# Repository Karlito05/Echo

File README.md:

# Echo
The best-sounding ortholinear keyboard.

## General Information
This project utilizes three main programs: [Ergogen](https://github.com/ergogen/ergogen), [Autodesk Fusion 360](https://www.autodesk.com/products/fusion-360/overview), and [KiCad](https://www.kicad.org/).

- The `config.yaml` file contains the Ergogen script used to generate the output files.
- 3D model files, including the case, switch plate, and keycaps, are located in the `./3D models` directory. Custom keycaps were modeled due to non-standard sizes.
- The entire keyboard is approximately 7 mm thick (excluding keycaps and switches).

### Why custom keycaps?
The keycaps sizes are not standard. For example in normal sets there is no R3 and R4 3U keycap. So I had to make my own.
## A Quick Overview of Ergogen
Ergogen is a generator utility for ergonomic keyboard layouts, including plates, cases, and PCBs. [Learn more about Ergogen here](https://docs.ergogen.xyz/)

In Ergogen, six main elements are used:
- **Meta**: Metadata
- **Units**: Defines unit-specific configurations
- **Zones**: Configurations for rows and columns
- **Outlines**: Outlines of the keyboard
- **PCBs**: Printed circuit board generation
- **Cases**: Case designs

Each of these elements is subdivided into more specific categories.

## How to Build from the Ergogen File
Follow these steps to build from the Ergogen file:

1. Ensure Ergogen and the `footprints` folder are in the same directory as `config.yaml`.
2. Open your terminal.
3. Navigate to the current working directory using `cd`.
4. Run the command:  
   ```bash
   ergogen .
   ```
This will generate an `output` folder containing the output files.

## Final Build
The keyboard has not been built yet. The plan includes:
- Switches: Lubed Akko Rosewood switches (hot-swap configuration)
- Lubed stabilizers
- Additional Sound-improving modifications

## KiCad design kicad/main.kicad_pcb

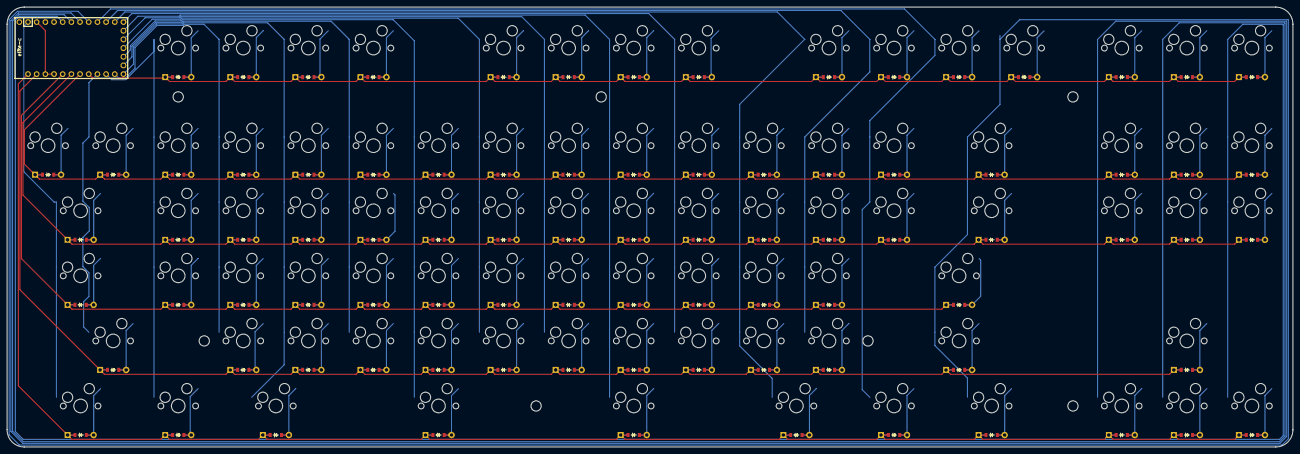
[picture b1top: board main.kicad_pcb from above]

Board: 2 copper layers, 376.4 x 128.8 mm, 174 parts (0 on the bottom side), 111 nets.

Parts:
D1, D2, D3, D4, D5, D6, D7, D8, D9, D10, D11, D12, D13, D14, D15, D16, D17, D18, D19, D20, D21, D22, D23, D24, D25, D26, D27, D28, D29, D30, D31, D32, D33, D34, D35, D36, D37, D38, D39, D40, D41, D42, D43, D44, D45, D46, D47, D48, D49, D50, D51, D52, D53, D54, D55, D56, D57, D58, D59, D60, D61, D62, D63, D64, D65, D66, D67, D68, D69, D70, D71, D72, D73, D74, D75, D76, D77, D78, D79, D80, D81, D82, D83, D84, D85, D86, D87: ComboDiode
S1, S2, S3, S4, S5, S6, S7, S8, S9, S10, S11, S12, S13, S14, S15, S16, S17, S18, S19, S20, S21, S22, S23, S24, S25, S26, S27, S28, S29, S30, S31, S32, S33, S34, S35, S36, S37, S38, S39, S40, S41, S42, S43, S44, S45, S46, S47, S48, S49, S50, S51, S52, S53, S54, S55, S56, S57, S58, S59, S60, S61, S62, S63, S64, S65, S66, S67, S68, S69, S70, S71, S72, S73, S74, S75, S76, S77, S78, S79, S80, S81, S82, S83, S84, S85, S86, S87: MX

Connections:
B0: S47.1, S48.1, S49.1, S55.1
B1: S44.1, S45.1, S61.1, S73.1
B2: S36.1, S37.1, S38.1, S39.1, S60.1, S71.1
B3: S40.1, S41.1, S42.1, S43.1, S72.1
B4: S4.1, S5.1, S6.1, S7.1, S64.1
B5: S8.1, S9.1, S10.1, S11.1, S57.1, S65.1
B6: S32.1, S33.1, S34.1, S35.1, S70.1
B7: S12.1, S13.1, S14.1, S15.1, S66.1
C6: D63.1, D64.1, D65.1, D66.1, D67.1, D68.1, D69.1, D70.1, D71.1, D72.1, D73.1, D74.1, D75.1, D76.1, D77.1
C7: S20.1, S21.1, S22.1, S23.1, S67.1
D0: D2.1, D6.1, D10.1, D14.1, D18.1, D22.1, D26.1, D30.1, D34.1, D38.1, D42.1, D44.1, D48.1, D53.1, D79.1, D83.1, D86.1
D1: D1.1, D5.1, D9.1, D13.1, D17.1, D21.1, D25.1, D29.1, D33.1, D37.1, D41.1, D47.1, D52.1
D2: D4.1, D8.1, D12.1, D16.1, D20.1, D24.1, D28.1, D32.1, D36.1, D40.1, D46.1, D51.1, D82.1
D3: D55.1, D56.1, D57.1, D58.1, D59.1, D60.1, D61.1, D62.1, D78.1, D81.1, D85.1
D4: D3.1, D7.1, D11.1, D15.1, D19.1, D23.1, D27.1, D31.1, D35.1, D39.1, D43.1, D45.1, D49.1, D50.1, D54.1, D80.1, D84.1, D87.1
D5: S16.1, S17.1, S18.1, S19.1, S58.1
D7: S46.1, S50.1
E6: S1.1, S2.1, S3.1, S56.1, S63.1
F0: S28.1, S29.1, S30.1, S31.1, S59.1, S69.1
F1: S24.1, S25.1, S26.1, S27.1, S68.1
F4: S77.1, S85.1, S86.1, S87.1
F5: S76.1, S81.1, S82.1, S83.1, S84.1
F6: S75.1, S78.1, S79.1, S80.1
F7: S51.1, S52.1, S53.1, S54.1, S62.1, S74.1
eight_eight: D31.2, S31.2
eight_i: D30.2, S30.2
eight_k: D29.2, S29.2
eight_m: D28.2, S28.2
eighth_f7: D69.2, S69.2
eleventh_dash: D43.2, S43.2
eleventh_f10: D72.2, S72.2
eleventh_openCurlyBrace: D42.2, S42.2
eleventh_questionMark: D40.2, S40.2
eleventh_quotes: D41.2, S41.2
fifteenth_scrLk: D76.2, S76.2
fifth_f4: D66.2, S66.2
fifth_five: D19.2, S19.2
fifth_g: D17.2, S17.2
fifth_spaceR: D59.2, S59.2
fifth_t: D18.2, S18.2
fifth_v: D16.2, S16.2
first_a: D1.2, S1.2
first_backspace: D54.2, S54.2
first_capsLock: D47.2, S47.2
first_ctrlL: D55.2, S55.2
first_delete: D79.2, S79.2
first_enter: D52.2, S52.2
first_esc: D49.2, S49.2
first_insert: D80.2, S80.2
first_lShift: D46.2, S46.2
first_left: D78.2, S78.2
first_one: D3.2, S3.2
first_pipe: D53.2, S53.2
first_q: D2.2, S2.2
first_rShift: D51.2, S51.2
first_tab: D48.2, S48.2
fourteenth_prntSc: D75.2, S75.2
fourth_c: D12.2, S12.2
fourth_f: D13.2, S13.2
fourth_f3: D65.2, S65.2
fourth_four: D15.2, S15.2
fourth_r: D14.2, S14.2
fourth_spaceL: D58.2, S58.2
ninth_comma: D32.2, S32.2
ninth_ctrlR: D62.2, S62.2
ninth_f8: D70.2, S70.2
ninth_l: D33.2, S33.2
ninth_nine: D35.2, S35.2
ninth_o: D34.2, S34.2
second_down: D81.2, S81.2
second_end: D83.2, S83.2
second_f1: D63.2, S63.2
second_home: D84.2, S84.2
second_s: D5.2, S5.2
second_tilde: D50.2, S50.2
second_two: D7.2, S7.2
second_up: D82.2, S82.2
second_w: D6.2, S6.2
second_windowsL: D56.2, S56.2
second_z: D4.2, S4.2
seventh_f6: D68.2, S68.2
seventh_j: D25.2, S25.2
seventh_n: D24.2, S24.2
seventh_seven: D27.2, S27.2
seventh_u: D26.2, S26.2
seventh_windowsR: D61.2, S61.2
sixteenth_pause: D77.2, S77.2
sixth_altGr: D60.2, S60.2
sixth_b: D20.2, S20.2
sixth_f5: D67.2, S67.2
sixth_h: D21.2, S21.2
sixth_six: D23.2, S23.2
sixth_y: D22.2, S22.2
tenth_dot: D36.2, S36.2
tenth_f9: D71.2, S71.2
tenth_p: D38.2, S38.2
tenth_semicolon: D37.2, S37.2
tenth_zero: D39.2, S39.2
third_alt: D57.2, S57.2
third_d: D9.2, S9.2
third_e: D10.2, S10.2
third_f2: D64.2, S64.2
third_pageDown: D86.2, S86.2
third_pageUp: D87.2, S87.2
third_right: D85.2, S85.2
third_three: D11.2, S11.2
third_x: D8.2, S8.2
thirteenth_f12: D74.2, S74.2
twelfth_closedCurlyBrace: D44.2, S44.2
twelfth_equals: D45.2, S45.2
twelfth_f11: D73.2, S73.2

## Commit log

2025-01-16 Uploaded V1
    all files needed to manufacture keyboard and custom keycaps
